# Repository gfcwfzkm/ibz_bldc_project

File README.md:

# ibz_bldc_project
A group project I participated in during my time in the IBZ side school. The task was any electronic project, so three other fellow students and I decided to build a BLDC driver.
I took care of the schematic, components and layout, another one handled assembly & basic testing, one did the programming / controlling and the last documented the whole project.
This project is not maintained but more a rough reference if anyone else wants to build something similar.
It uses the L6234 as BLDC driver and offers either HALL-Sensor Input or Back-EMF (selectable via jumpers) as well as enough test points to probe on. It was laid out to be a rather flexible but basic platform to explore BLDC Motor driving a bit more.

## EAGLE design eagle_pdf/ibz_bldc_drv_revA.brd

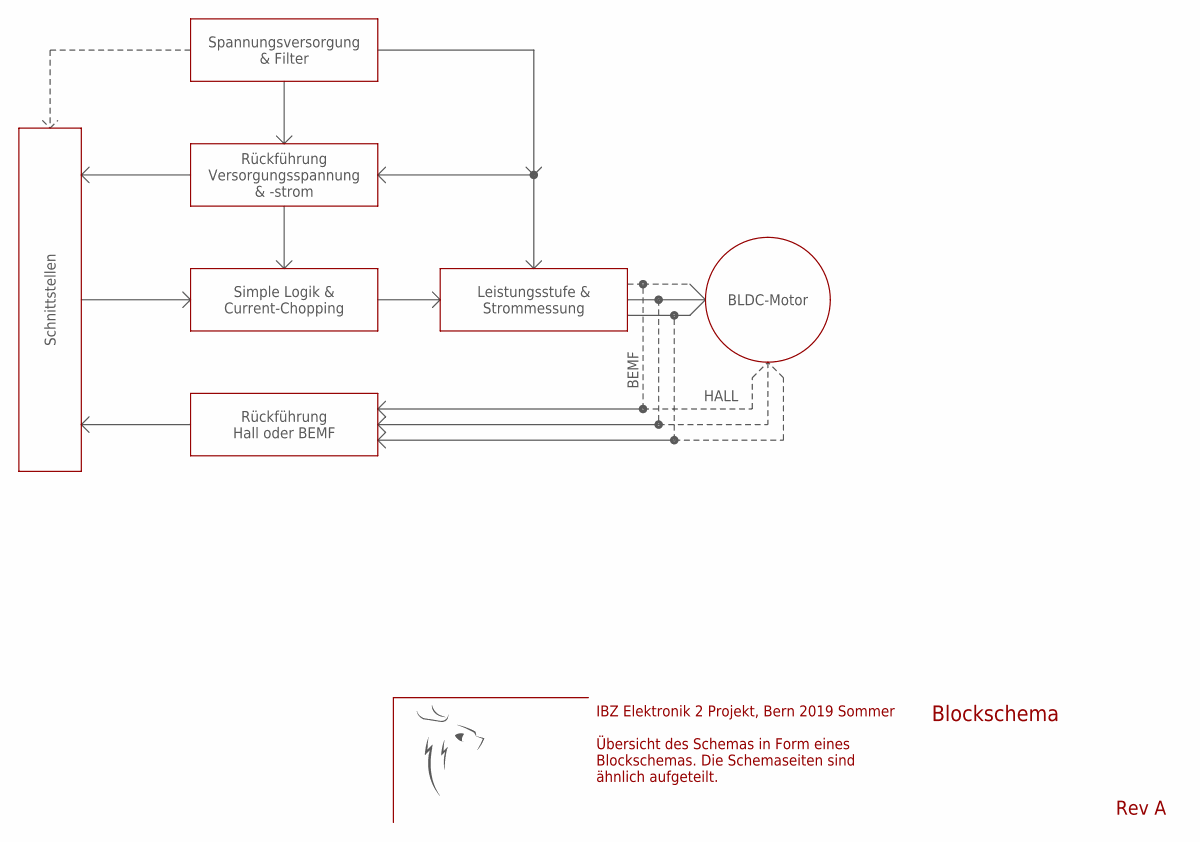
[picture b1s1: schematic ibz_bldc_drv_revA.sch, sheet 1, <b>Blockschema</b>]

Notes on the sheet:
Spannungsversorgung & Filter
BLDC-Motor
Leistungsstufe & Strommessung
Simple Logik & Current-Chopping
Schnittstellen
Rückführung Versorgungsspannung & -strom
Rückführung Hall oder BEMF
BEMF
HALL
Blockschema
Rev A
IBZ Elektronik 2 Projekt, Bern 2019 Sommer Übersicht des Schemas in Form eines Blockschemas. Die Schemaseiten sind ähnlich aufgeteilt.

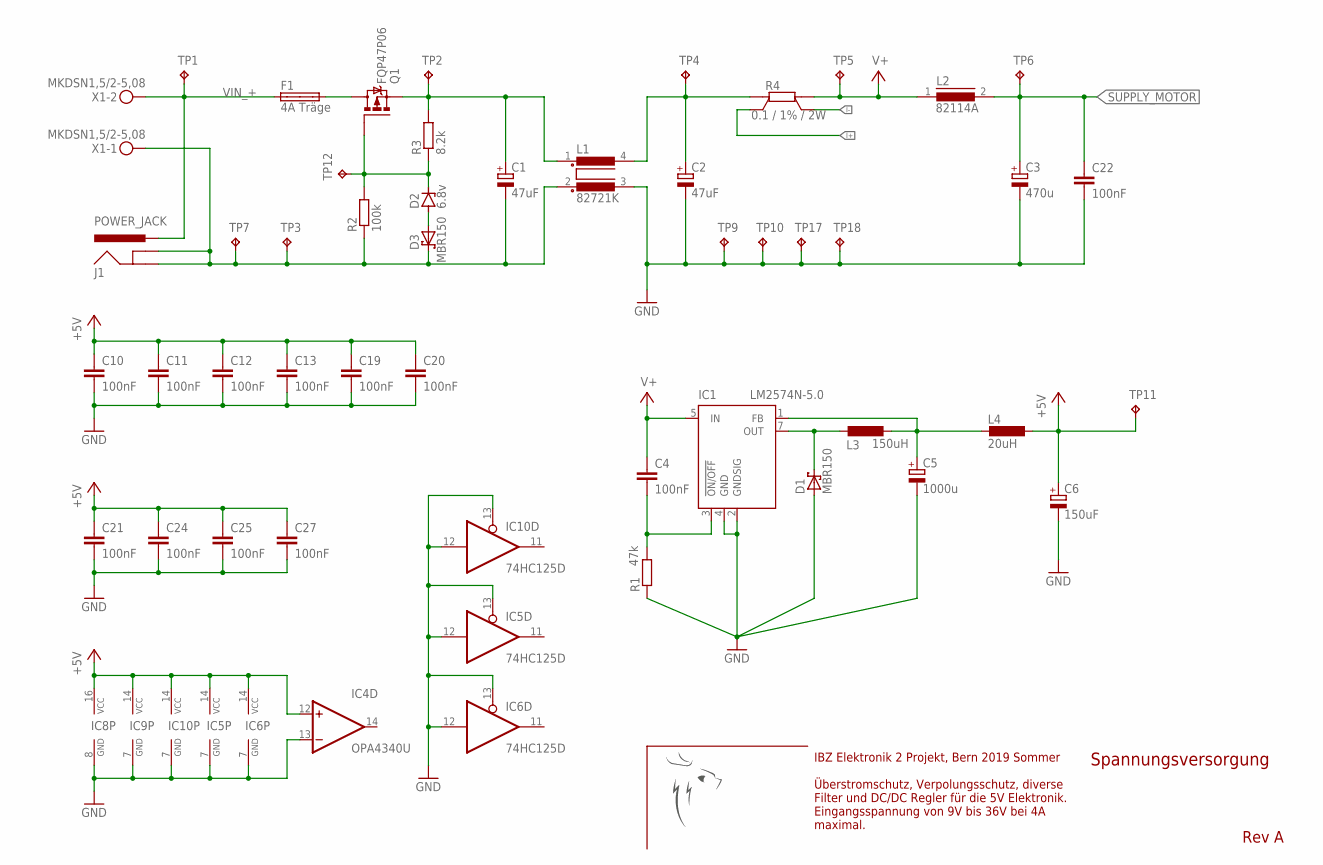
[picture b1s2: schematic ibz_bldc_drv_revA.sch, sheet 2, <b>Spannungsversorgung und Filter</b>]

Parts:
C1, C2: 47uF; E22-9
C3: 470u; E22-9
C4, C10, C11, C12, C13, C19, C20, C21, C22, C24, C25, C27: 100nF; C1206
C5: 1000u; E5-10,5
C6: 150uF; 153CLV-1010
D1, D3: MBR150; DO41-7
D2: 6.8v; DO41Z10
F1: 4A Träge; SHK20Q
IC1: LM2574N-5.0; DIL08
IC4: OPA4340U; SO14
IC5, IC6, IC10: 74HC125D; SO14
IC8: 74HC123D; SO16
IC9: 74HC08D; SO14
J1: POWER_JACK; POWER_JACK_PTH
L1: 82721K
L2: 82114A
L3: 150uH; IR-2
L4: 20uH; L5038P
Q1: FQP47P06; TO220BV
R1: 47k; R1206
R2: 100k; R1206
R3: 8.2k; R1206
R4: 0.1 / 1% / 2W; PMA-B
TP1, TP2, TP3, TP4, TP5, TP6, TP7, TP9, TP10, TP11, TP12, TP17, TP18: TPPAD1-13; P1-13
X1: MKDSN1,5/2-5,08

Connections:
+5V: C6.+, C10.1, C11.1, C12.1, C13.1, C19.1, C20.1, C21.1, C24.1, C25.1, C27.1, IC4.12 (+IN), IC5.14 (VCC), IC6.14 (VCC), IC8.16 (VCC), IC9.14 (VCC), IC10.14 (VCC), L4.1, TP11.TP; also elsewhere on the board
GND: C2.-, C3.-, C5.-, C6.-, C10.2, C11.2, C12.2, C13.2, C19.2, C20.2, C21.2, C22.2, C24.2, C25.2, C27.2, D1.A, IC1.2 (GNDSIG), IC1.4 (GND), IC4.13 (-IN), IC5.7 (GND), IC5.12 (I), IC5.13 (OE), IC6.7 (GND), IC6.12 (I), IC6.13 (OE), IC8.8 (GND), IC9.7 (GND), IC10.7 (GND), IC10.12 (I), IC10.13 (OE), L1.3 (4), R1.1, TP9.TP, TP10.TP, TP17.TP, TP18.TP; also elsewhere on the board
I+: R4.SB; also elsewhere on the board
I-: R4.SA; also elsewhere on the board
unnamed: C1.-, D3.C, J1.GND, J1.GNDBREAK, L1.2 (3), R2.1, TP3.TP, TP7.TP, X1.1
unnamed: C1.+, L1.1, Q1.S, R3.2, TP2.TP
unnamed: C2.+, L1.4 (2), R4.B, TP4.TP
unnamed: C4.2, IC1.3 (!ON/OFF), R1.2
unnamed: C5.+, IC1.1 (FB), L3.1, L4.2
unnamed: D1.C, IC1.7 (OUT), L3.2
unnamed: F1.2A, Q1.D
unnamed: D2.C, Q1.G, R2.2, R3.1, TP12.TP
unnamed: D2.A, D3.A
SUPPLY_MOTOR: C3.+, C22.1, L2.2, TP6.TP; also elsewhere on the board
V+: C4.1, IC1.5 (IN), L2.1, R4.A, TP5.TP; also elsewhere on the board
VIN_+: F1.1A, J1.PWR, TP1.TP, X1.2

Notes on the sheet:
IBZ Elektronik 2 Projekt, Bern 2019 Sommer Überstromschutz, Verpolungsschutz, diverse Filter und DC/DC Regler für die 5V Elektronik. Eingangsspannung von 9V bis 36V bei 4A maximal.
Spannungsversorgung
Rev A

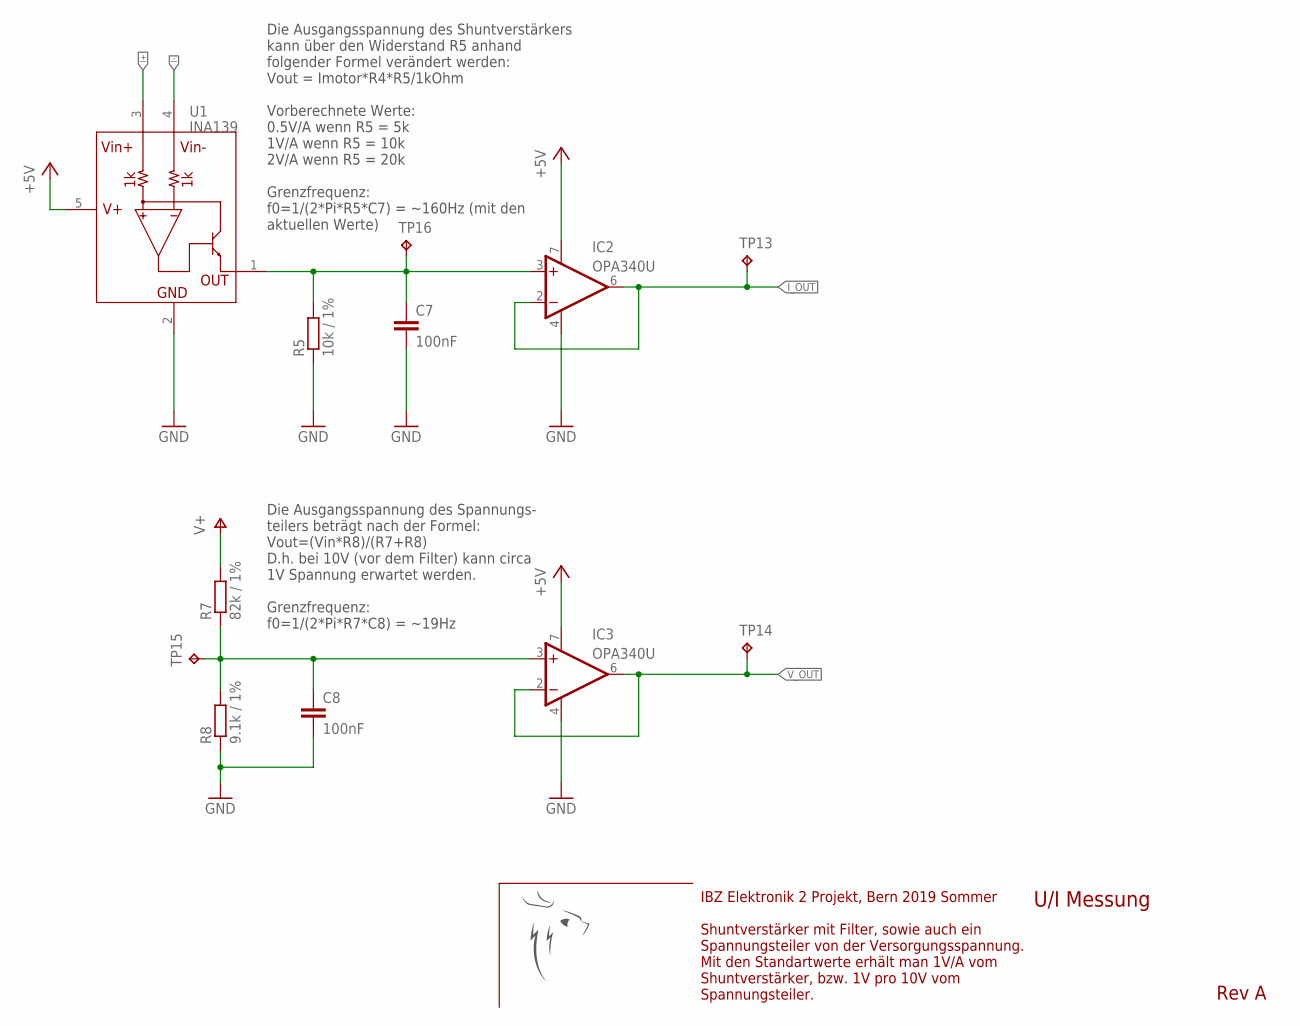
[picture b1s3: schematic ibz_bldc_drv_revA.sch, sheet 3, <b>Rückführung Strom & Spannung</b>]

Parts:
C7, C8: 100nF; C1206
IC2, IC3: OPA340U; SO08
R5: 10k / 1%; R1206
R7: 82k / 1%; R1206
R8: 9.1k / 1%; R1206
TP13, TP14, TP15, TP16: TPPAD1-13; P1-13
U1: INA139; SOT23-5

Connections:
+5V: IC2.7 (V+), IC3.7 (V+), U1.5 (V+); also elsewhere on the board
GND: C7.2, C8.2, IC2.4 (V-), IC3.4 (V-), R5.1, R8.1, U1.2 (GND); also elsewhere on the board
I+: U1.3 (VIN+); also elsewhere on the board
I-: U1.4 (VIN-); also elsewhere on the board
I_OUT: IC2.2 (-IN), IC2.6 (OUT), TP13.TP; also elsewhere on the board
unnamed: C7.1, IC2.3 (+IN), R5.2, TP16.TP, U1.1 (OUT)
unnamed: C8.1, IC3.3 (+IN), R7.1, R8.2, TP15.TP
V+: R7.2; also elsewhere on the board
V_OUT: IC3.2 (-IN), IC3.6 (OUT), TP14.TP; also elsewhere on the board

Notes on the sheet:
Die Ausgangsspannung des Shuntverstärkers kann über den Widerstand R5 anhand folgender Formel verändert werden: Vout = Imotor*R4*R5/1kOhm Vorberechnete Werte: 0.5V/A wenn R5 = 5k 1V/A wenn R5 = 10k 2V/A wenn R5 = 20k Grenzfrequenz: f0=1/(2*Pi*R5*C7) = ~160Hz (mit den aktuellen Werte)
Die Ausgangsspannung des Spannungs- teilers beträgt nach der Formel: Vout=(Vin*R8)/(R7+R8) D.h. bei 10V (vor dem Filter) kann circa 1V Spannung erwartet werden. Grenzfrequenz: f0=1/(2*Pi*R7*C8) = ~19Hz
IBZ Elektronik 2 Projekt, Bern 2019 Sommer Shuntverstärker mit Filter, sowie auch ein Spannungsteiler von der Versorgungsspannung. Mit den Standartwerte erhält man 1V/A vom Shuntverstärker, bzw. 1V pro 10V vom Spannungsteiler.
U/I Messung
Rev A

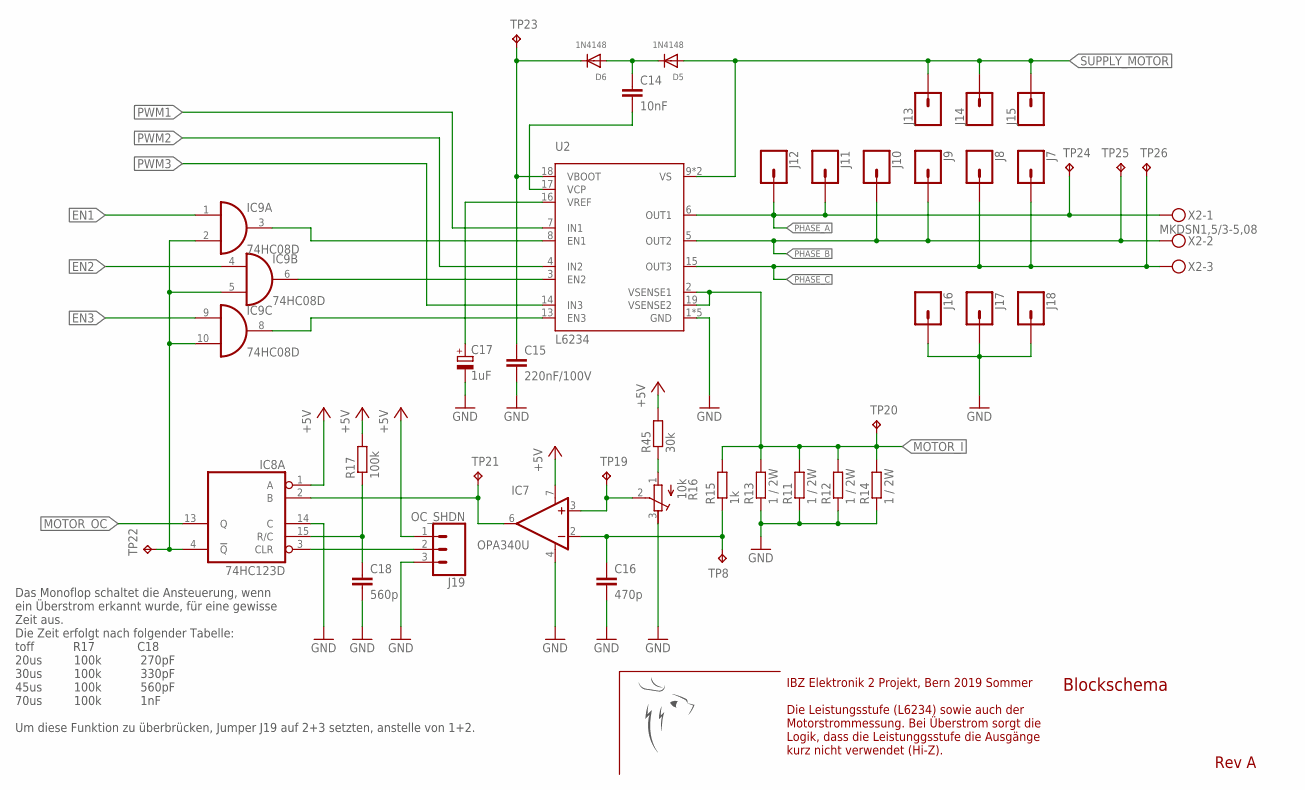
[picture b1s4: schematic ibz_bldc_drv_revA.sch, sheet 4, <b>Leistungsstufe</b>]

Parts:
C14: 10nF; C1206
C15: 220nF/100V; C1206
C16: 470p; C1206
C17: 1uF; 153CLV-0505
C18: 560p; C1206
D5, D6: 1N4148; SMADIODE
IC7: OPA340U; SO08
IC8: 74HC123D; SO16
IC9: 74HC08D; SO14
J7, J8, J9, J10, J11, J12, J13, J14, J15, J16, J17, J18: CONN_01PTH_2MM; 1X01_2MM
J19: OC_SHDN; 1X03
R11, R12, R13, R14: 1 / 2W; 0411/15
R15: 1k; R1206
R16: 10k; RTRIM64W
R17: 100k; R1206
R45: 30k; R1206
TP8, TP19, TP20, TP21, TP22, TP23, TP24, TP25, TP26: TPPAD1-13; P1-13
U2: L6234; POWERSO20
X2: MKDSN1,5/3-5,08

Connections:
+5V: IC7.7 (V+), IC8.1 (A), J19.1, R17.2, R45.2; also elsewhere on the board
EN1: IC9.1 (I0); also elsewhere on the board
EN2: IC9.4 (I0); also elsewhere on the board
EN3: IC9.9 (I0); also elsewhere on the board
GND: C15.2, C16.2, C17.-, C18.2, IC7.4 (V-), IC8.14 (C), J16.1, J17.1, J18.1, J19.3, R11.1, R12.1, R13.1, R14.1, R16.3 (E), U2.1 (GND), U2.10 (GND), U2.11 (GND), U2.20 (GND), U2.PAD (GND); also elsewhere on the board
MOTOR_I: R11.2, R12.2, R13.2, R14.2, R15.2, TP20.TP, U2.2 (VSENSE1), U2.19 (VSENSE2); also elsewhere on the board
MOTOR_OC: IC8.13 (Q); also elsewhere on the board
unnamed: C14.1, D5.C, D6.A
unnamed: IC9.3 (O), U2.8 (EN1)
unnamed: C15.1, D6.C, TP23.TP, U2.18 (VBOOT)
unnamed: C14.2, U2.17 (VCP)
unnamed: C17.+, U2.16 (VREF)
unnamed: IC9.6 (O), U2.3 (EN2)
unnamed: IC9.8 (O), U2.13 (EN3)
unnamed: C16.1, IC7.2 (-IN), R15.1, TP8.TP
unnamed: IC8.4 (!Q), IC9.2 (I1), IC9.5 (I1), IC9.10 (I1), TP22.TP
unnamed: IC7.6 (OUT), IC8.2 (B), TP21.TP
unnamed: C18.1, IC8.15 (R/C), R17.1
unnamed: IC8.3 (CLR), J19.2
unnamed: IC7.3 (+IN), R16.2 (S), TP19.TP
unnamed: R16.1 (A), R45.1
PHASE_A: J11.1, J12.1, TP24.TP, U2.6 (OUT1), X2.1; also elsewhere on the board
PHASE_B: J9.1, J10.1, TP25.TP, U2.5 (OUT2), X2.2; also elsewhere on the board
PHASE_C: J7.1, J8.1, TP26.TP, U2.15 (OUT3), X2.3; also elsewhere on the board
PWM1: U2.7 (IN1); also elsewhere on the board
PWM2: U2.4 (IN2); also elsewhere on the board
PWM3: U2.14 (IN3); also elsewhere on the board
SUPPLY_MOTOR: D5.A, J13.1, J14.1, J15.1, U2.9 (VS), U2.12 (VS); also elsewhere on the board

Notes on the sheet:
IBZ Elektronik 2 Projekt, Bern 2019 Sommer Die Leistungsstufe (L6234) sowie auch der Motorstrommessung. Bei Überstrom sorgt die Logik, dass die Leistunggsstufe die Ausgänge kurz nicht verwendet (Hi-Z).
Blockschema
Rev A
Das Monoflop schaltet die Ansteuerung, wenn ein Überstrom erkannt wurde, für eine gewisse Zeit aus. Die Zeit erfolgt nach folgender Tabelle: toff R17 C18 20us 100k 270pF 30us 100k 330pF 45us 100k 560pF 70us 100k 1nF Um diese Funktion zu überbrücken, Jumper J19 auf 2+3 setzten, anstelle von 1+2.

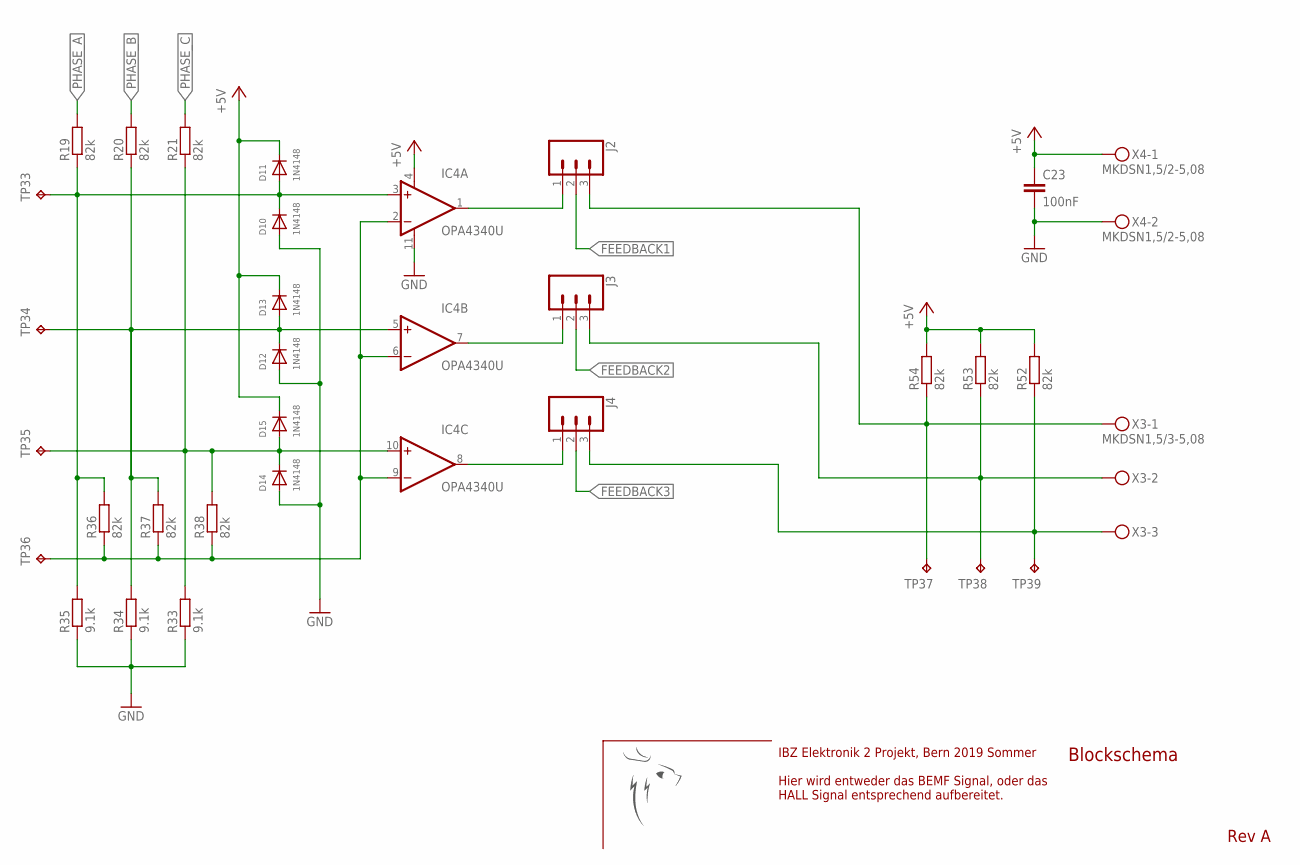
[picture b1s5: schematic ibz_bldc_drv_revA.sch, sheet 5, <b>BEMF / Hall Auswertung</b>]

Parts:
C23: 100nF; C1206
D10, D11, D12, D13, D14, D15: 1N4148; SMADIODE
IC4: OPA4340U; SO14
J2, J3, J4: CONN_03; 1X03
R19, R20, R21, R36, R37, R38, R52, R53, R54: 82k; R1206
R33, R34, R35: 9.1k; R1206
TP33, TP34, TP35, TP36, TP37, TP38, TP39: TPPAD1-13; P1-13
X3: MKDSN1,5/3-5,08
X4: MKDSN1,5/2-5,08

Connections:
+5V: C23.1, D11.C, D13.C, D15.C, IC4.4 (V+), R52.2, R53.2, R54.2, X4.1; also elsewhere on the board
FEEDBACK1: J2.2; also elsewhere on the board
FEEDBACK2: J3.2; also elsewhere on the board
FEEDBACK3: J4.2; also elsewhere on the board
GND: C23.2, D10.A, D12.A, D14.A, IC4.11 (V-), R33.1, R34.1, R35.1, X4.2; also elsewhere on the board
unnamed: D14.C, D15.A, IC4.10 (+IN), R21.1, R33.2, R38.2, TP35.TP
unnamed: D10.C, D11.A, IC4.3 (+IN), R19.1, R35.2, R36.2, TP33.TP
unnamed: D12.C, D13.A, IC4.5 (+IN), R20.1, R34.2, R37.2, TP34.TP
unnamed: IC4.1 (OUT), J2.1
unnamed: IC4.2 (-IN), IC4.6 (-IN), IC4.9 (-IN), R36.1, R37.1, R38.1, TP36.TP
unnamed: IC4.7 (OUT), J3.1
unnamed: IC4.8 (OUT), J4.1
unnamed: J2.3, R54.1, TP37.TP, X3.1
unnamed: J3.3, R53.1, TP38.TP, X3.2
unnamed: J4.3, R52.1, TP39.TP, X3.3
PHASE_A: R19.2; also elsewhere on the board
PHASE_B: R20.2; also elsewhere on the board
PHASE_C: R21.2; also elsewhere on the board

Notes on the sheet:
IBZ Elektronik 2 Projekt, Bern 2019 Sommer Hier wird entweder das BEMF Signal, oder das HALL Signal entsprechend aufbereitet.
Blockschema
Rev A

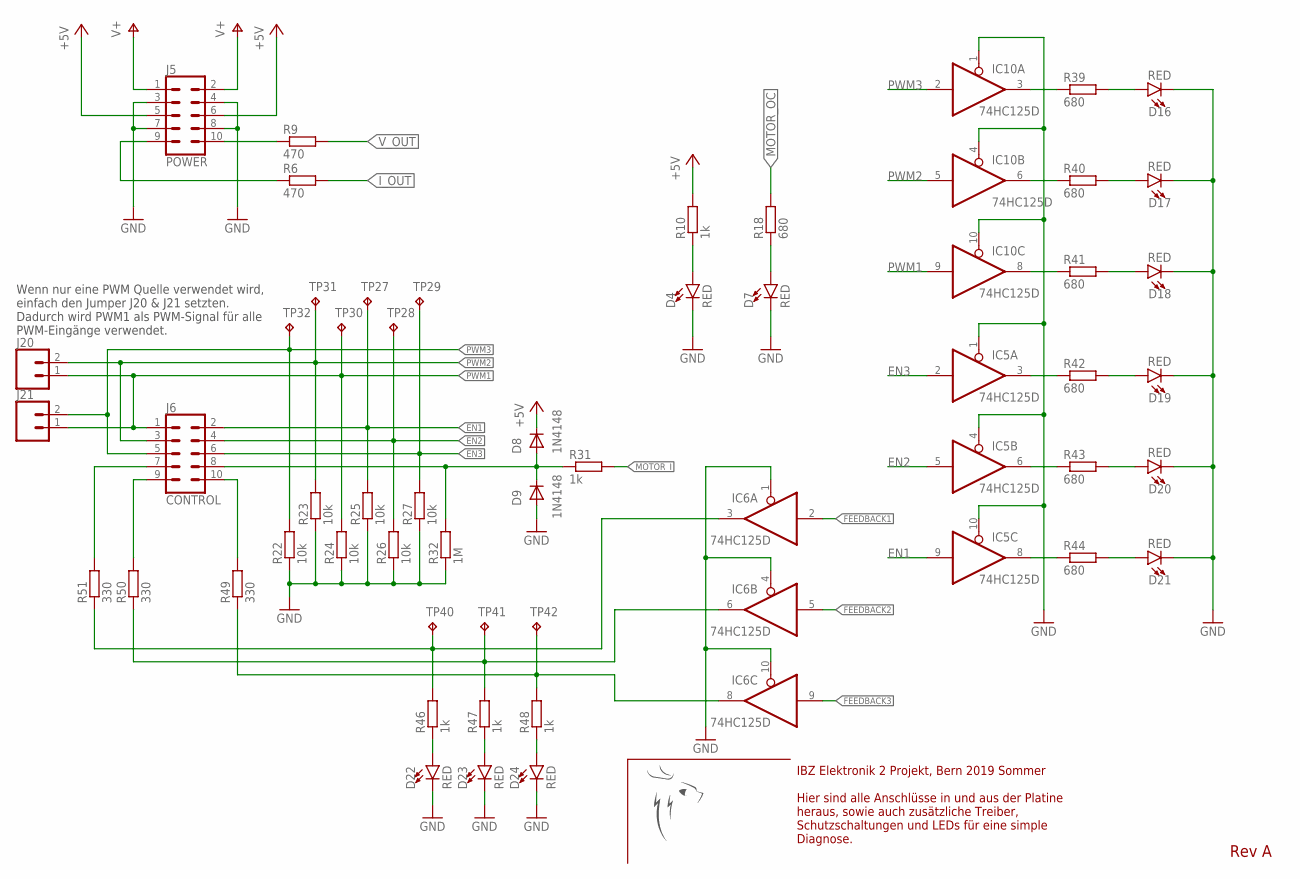
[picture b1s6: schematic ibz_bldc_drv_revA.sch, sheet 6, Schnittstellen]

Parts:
D4, D7, D16, D17, D18, D19, D20, D21, D22, D23, D24: RED; LED-1206
D8, D9: 1N4148; SMADIODE
IC5, IC6, IC10: 74HC125D; SO14
J5: POWER; 2X5-SHROUDED
J6: CONTROL; 2X5-SHROUDED
J20, J21: CONN_02; 1X02
R6, R9: 470; M1206
R10, R31, R46, R47, R48: 1k; R1206
R18, R39, R40, R41, R42, R43, R44: 680; R1206
R22, R23, R24, R25, R26, R27: 10k; R1206
R32: 1M; R1206
R49, R50, R51: 330; R1206
TP27, TP28, TP29, TP30, TP31, TP32, TP40, TP41, TP42: TPPAD1-13; P1-13

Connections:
+5V: D8.C, J5.5, J5.6, R10.2; also elsewhere on the board
EN1: IC5.9 (I), J6.2, R25.2, TP27.TP; also elsewhere on the board
EN2: IC5.5 (I), J6.4, R26.2, TP28.TP; also elsewhere on the board
EN3: IC5.2 (I), J6.6, R27.2, TP29.TP; also elsewhere on the board
FEEDBACK1: IC6.2 (I); also elsewhere on the board
FEEDBACK2: IC6.5 (I); also elsewhere on the board
FEEDBACK3: IC6.9 (I); also elsewhere on the board
GND: D4.C, D7.C, D9.A, D16.C, D17.C, D18.C, D19.C, D20.C, D21.C, D22.C, D23.C, D24.C, IC5.1 (OE), IC5.4 (OE), IC5.10 (OE), IC6.1 (OE), IC6.4 (OE), IC6.10 (OE), IC10.1 (OE), IC10.4 (OE), IC10.10 (OE), J5.3, J5.4, J5.7, J5.8, R22.1, R23.1, R24.1, R25.1, R26.1, R27.1, R32.1; also elsewhere on the board
I_OUT: R6.2; also elsewhere on the board
MOTOR_I: R31.2; also elsewhere on the board
MOTOR_OC: R18.2; also elsewhere on the board
unnamed: D4.A, R10.1
unnamed: J5.9, R6.1
unnamed: J5.10, R9.1
unnamed: D7.A, R18.1
unnamed: D8.A, D9.C, J6.8, R31.1, R32.2
unnamed: IC10.3 (O), R39.1
unnamed: IC10.6 (O), R40.1
unnamed: IC10.8 (O), R41.1
unnamed: IC5.3 (O), R42.1
unnamed: D19.A, R42.2
unnamed: D18.A, R41.2
unnamed: D17.A, R40.2
unnamed: D16.A, R39.2
unnamed: IC5.6 (O), R43.1
unnamed: D20.A, R43.2
unnamed: IC5.8 (O), R44.1
unnamed: D21.A, R44.2
unnamed: J6.10, R49.2
unnamed: IC6.8 (O), R48.2, R49.1, TP42.TP
unnamed: IC6.6 (O), R47.2, R50.1, TP41.TP
unnamed: IC6.3 (O), R46.2, R51.1, TP40.TP
unnamed: D22.A, R46.1
unnamed: D23.A, R47.1
unnamed: D24.A, R48.1
unnamed: J6.9, R50.2
unnamed: J6.7, R51.2
PWM1: IC10.9 (I), J6.1, J20.1, J21.1, R24.2, TP30.TP; also elsewhere on the board
PWM2: IC10.5 (I), J6.3, J20.2, R23.2, TP31.TP; also elsewhere on the board
PWM3: IC10.2 (I), J6.5, J21.2, R22.2, TP32.TP; also elsewhere on the board
V+: J5.1, J5.2; also elsewhere on the board
V_OUT: R9.2; also elsewhere on the board

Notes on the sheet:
Wenn nur eine PWM Quelle verwendet wird, einfach den Jumper J20 & J21 setzten. Dadurch wird PWM1 als PWM-Signal für alle PWM-Eingänge verwendet.
IBZ Elektronik 2 Projekt, Bern 2019 Sommer Hier sind alle Anschlüsse in und aus der Platine heraus, sowie auch zusätzliche Treiber, Schutzschaltungen und LEDs für eine simple Diagnose.
Rev A

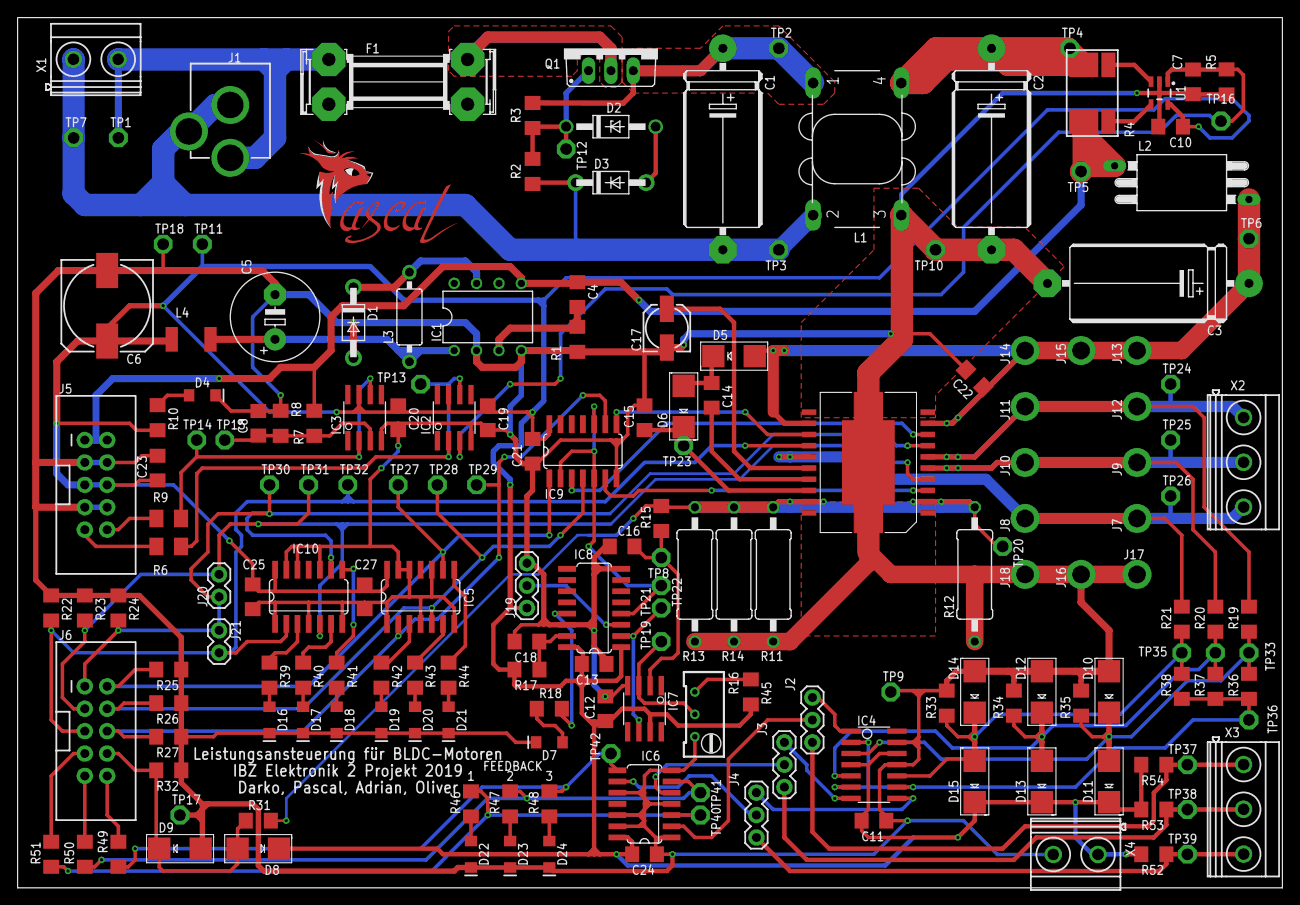
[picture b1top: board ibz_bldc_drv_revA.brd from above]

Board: 2 copper layers, 143.5 x 98.7 mm, 185 parts (0 on the bottom side), 84 nets.

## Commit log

2021-05-06 Creation of the folder
2021-05-06 Initial upload of the schematic & layout
2021-05-06 Initial upload of image and video

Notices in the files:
parts and their libraries:
SparkFun-LED: Licensing: Creative Commons ShareAlike 4.0 International - https://creativecommons.org/licenses/by-sa/4.0
